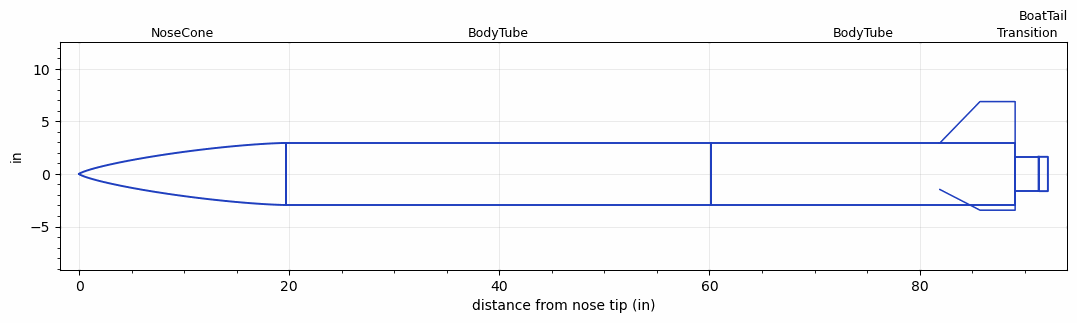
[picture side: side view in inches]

<RASAeroDocument>
 <RocketDesign>
  <NoseCone>
   <Length>19.68505</Length>
   <Diameter>5.905515</Diameter>
   <Shape>Von Karman Ogive</Shape>
   <BluntRadius>0.1181103</BluntRadius>
   <Location>0</Location>
  </NoseCone>
  <BodyTube>
   <Length>40.496085</Length>
   <Diameter>5.905515</Diameter>
   <Location>19.68505</Location>
  </BodyTube>
  <BodyTube>
   <Length>28.913401</Length>
   <Diameter>5.905515</Diameter>
   <Location>60.181135</Location>
   <RailGuideDiameter>0.38188997</RailGuideDiameter>
   <RailGuideHeight>0.29527575</RailGuideHeight>
   <Fin>
    <Count>3</Count>
    <Chord>7.1653582</Chord>
    <Span>3.93701</Span>
    <SweepDistance>3.8188997</SweepDistance>
    <TipChord>3.3464585</TipChord>
    <Thickness>0.26771668</Thickness>
    <LERadius>0.0393701</LERadius>
    <Location>7.1653582</Location>
    <AirfoilSection>Subsonic NACA</AirfoilSection>
   </Fin>
  </BodyTube>
  <Transition>
   <Length>2.2322847</Length>
   <Diameter>3.2677183</Diameter>
   <Location>89.094536</Location>
   <RearDiameter>3.2677183</RearDiameter>
  </Transition>
  <BoatTail>
   <Length>0.88582725</Length>
   <Diameter>3.2677183</Diameter>
   <Location>91.326821</Location>
   <RearDiameter>3.2637813</RearDiameter>
  </BoatTail>
  <Surface>Smooth (Zero Roughness)</Surface>
  <CP>56.384418</CP>
  <ModifiedBarrowman>True</ModifiedBarrowman>
  <Turbulence>False</Turbulence>
  <SustainerNozzle>2.362206</SustainerNozzle>
  <FileVersion>2</FileVersion>
  <UseBooster1>False</UseBooster1>
  <UseBooster2>False</UseBooster2>
 </RocketDesign>
 <LaunchSite>
  <Altitude>0.0</Altitude>
  <Pressure>29.92469</Pressure>
  <RodAngle>0</RodAngle>
  <RodLength>19.68504</RodLength>
  <Temperature>59.0</Temperature>
  <WindSpeed>11.1847</WindSpeed>
 </LaunchSite>
 <Recovery>
  <Altitude1>0</Altitude1>
  <Size1>12.007881</Size1>
  <EventType1>Apogee</EventType1>
  <CD1>1.6</CD1>
  <Event1>True</Event1>
  <DeviceType1>Parachute</DeviceType1>
  <Altitude2>984.252</Altitude2>
  <Size2>60.000032</Size2>
  <EventType2>Altitude</EventType2>
  <CD2>2.2</CD2>
  <Event2>False</Event2>
  <DeviceType2>Parachute</DeviceType2>
 </Recovery>
 <SimulationList>
  <Simulation>
   <SustainerEngine>8429-M2020-IM-P</SustainerEngine>
   <SustainerLaunchWt>31.515624</SustainerLaunchWt>
   <SustainerNozzleDiameter>2.362206</SustainerNozzleDiameter>
   <SustainerCG>59.755904</SustainerCG>
   <SustainerIgnitionDelay>0</SustainerIgnitionDelay>
   <Booster1SeparationDelay>0</Booster1SeparationDelay>
   <Booster1IgnitionDelay>0</Booster1IgnitionDelay>
   <IncludeBooster1>False</IncludeBooster1>
   <Booster2Delay>0</Booster2Delay>
   <IncludeBooster2>False</IncludeBooster2>
  </Simulation>
 </SimulationList>
</RASAeroDocument>
